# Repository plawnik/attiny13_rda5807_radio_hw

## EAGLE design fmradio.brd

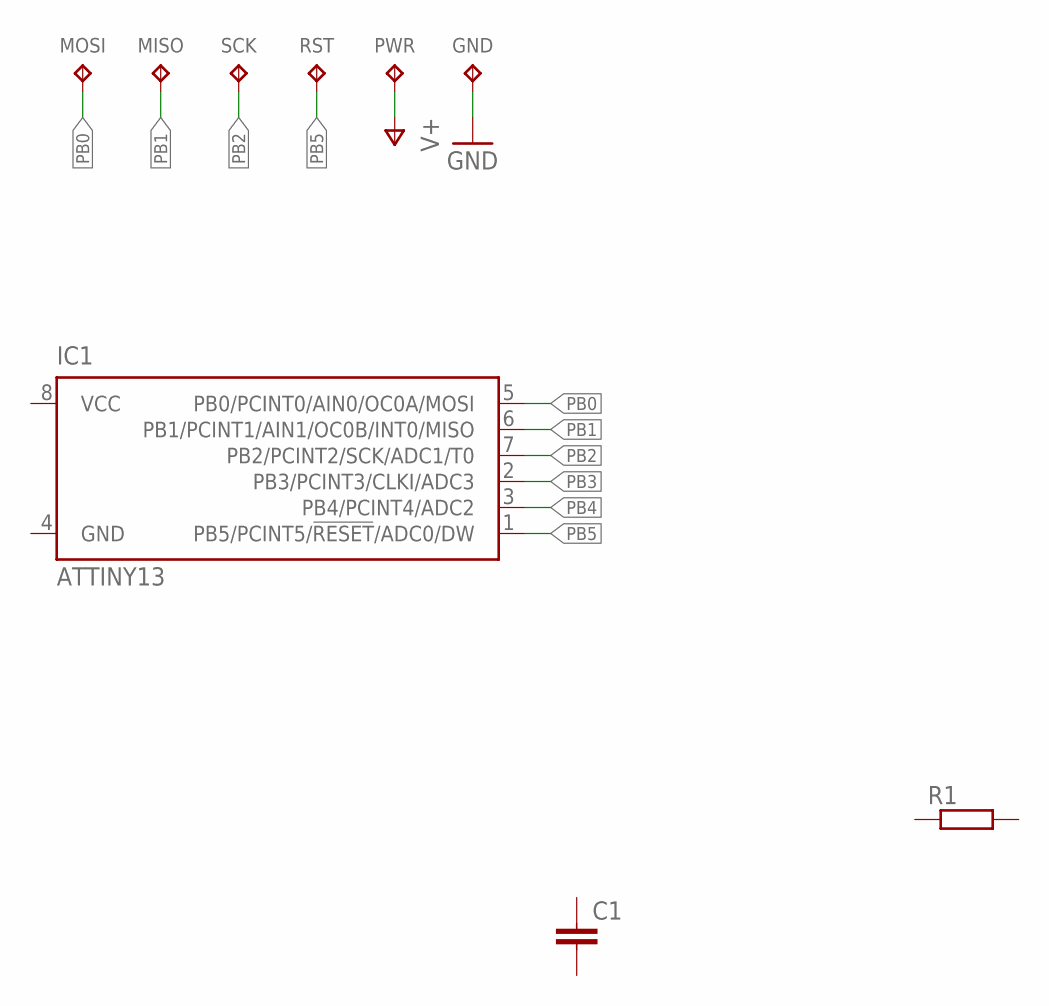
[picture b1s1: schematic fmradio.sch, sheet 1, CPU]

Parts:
C1: C0603NOMINAL; C0603_NOMINAL
GND: TPTP10R; TP10R
IC1: ATTINY13; 8S1
MISO: TPTP10R; TP10R
MOSI: TPTP10R; TP10R
PWR: TPTP10R; TP10R
R1: R0603NOMINAL; R0603_NOMINAL
RST: TPTP15R; TP15R
SCK: TPTP10R; TP10R

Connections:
GND: GND.TP; also elsewhere on the board
PB0: IC1.5 (PB0/PCINT0/AIN0/OC0A/MOSI), MOSI.TP
PB1: IC1.6 (PB1/PCINT1/AIN1/OC0B/INT0/MISO), MISO.TP
PB2: IC1.7 (PB2/PCINT2/SCK/ADC1/T0), SCK.TP
PB3: IC1.2 (PB3/PCINT3/CLKI/ADC3)
PB4: IC1.3 (PB4/PCINT4/ADC2)
PB5: IC1.1 (PB5/PCINT5/!RESET!/ADC0/DW), RST.TP
V+: PWR.TP; also elsewhere on the board

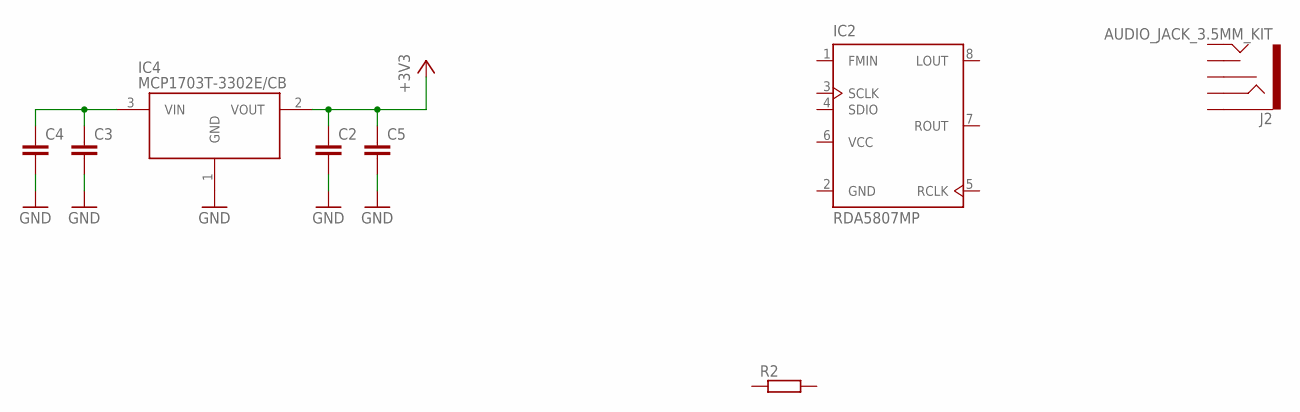
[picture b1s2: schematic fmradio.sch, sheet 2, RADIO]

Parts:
C2, C3, C4, C5: C0603NOMINAL; C0603_NOMINAL
IC2: RDA5807MP; 8S1
IC4: MCP1703T-3302E/CB; SOT95P255X145-3N
J2: AUDIO_JACK_3.5MM_KIT; AUDIO-JACK-KIT
R2: R0603NOMINAL; R0603_NOMINAL

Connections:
+3V3: C2.1, C5.1, IC4.2 (VOUT)
GND: C2.2, C3.2, C4.2, C5.2, IC4.1 (GND); also elsewhere on the board
unnamed: C3.1, C4.1, IC4.3 (VIN)

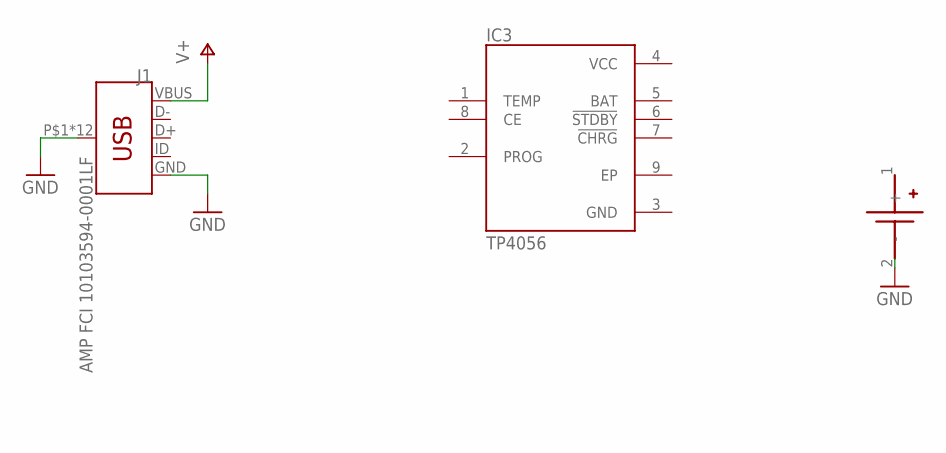
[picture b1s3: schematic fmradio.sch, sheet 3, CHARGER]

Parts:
IC3: TP4056; SOP127P600X175-9N
J1: AMP FCI 10103594-0001LF; USB-MICROB-PTH
U$1: BLOSSOM-BLM-18650-1PCS

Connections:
GND: J1.GND, J1.P$1 (SHIELD), J1.P$2 (SHIELD), J1.P$3 (SHIELD), J1.P$4 (SHIELD), J1.P$6 (SHIELD), J1.P$8 (SHIELD), J1.P$10 (SHIELD), J1.P$12 (SHIELD), J1.SHEILD2 (SHIELD), J1.SHIELD, J1.SHIELD3 (SHIELD), J1.SHIELD4 (SHIELD), U$1.2 (-); also elsewhere on the board
V+: J1.VBUS; also elsewhere on the board

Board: 2 copper layers, 20 parts (0 on the bottom side), 8 nets, no tracks yet.

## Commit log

2023-04-20 initial
2023-04-20 lbt test
2023-04-20 libs

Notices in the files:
parts and their libraries:
SparkFun-Connectors: Licensing: Creative Commons ShareAlike 4.0 International - https://creativecommons.org/licenses/by-sa/4.0
